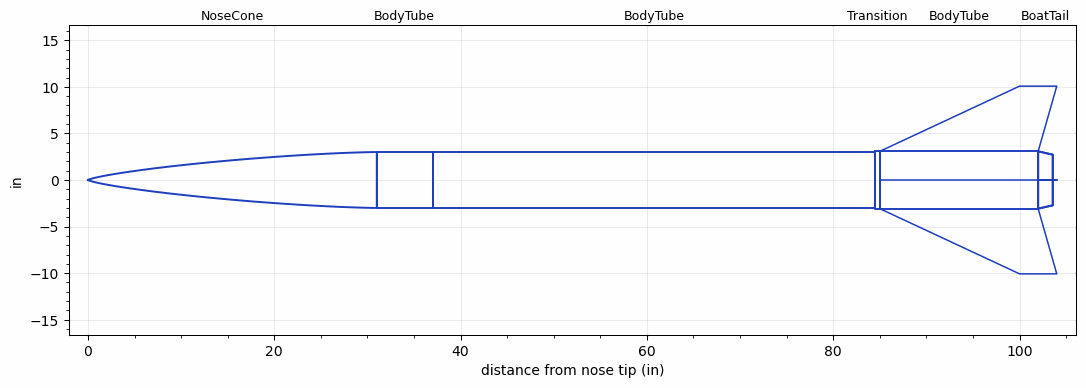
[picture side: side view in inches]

<RASAeroDocument>
 <FileVersion>2</FileVersion>
 <RocketDesign>
  <NoseCone>
   <Length>30.9999</Length>
   <Diameter>6</Diameter>
   <Shape>Von Karman Ogive</Shape>
   <BluntRadius>0.08</BluntRadius>
   <Location>0</Location>
  </NoseCone>
  <BodyTube>
   <Length>6</Length>
   <Diameter>6</Diameter>
   <Location>30.9999</Location>
  </BodyTube>
  <BodyTube>
   <Length>47.5</Length>
   <Diameter>6</Diameter>
   <RailGuideDiameter>0.63</RailGuideDiameter>
   <RailGuideHeight>0.44</RailGuideHeight>
   <Location>36.9999</Location>
  </BodyTube>
  <Transition>
   <Length>0.5</Length>
   <Diameter>6.15</Diameter>
   <Location>84.4999</Location>
   <RearDiameter>6.15</RearDiameter>
  </Transition>
  <BodyTube>
   <Length>17</Length>
   <Diameter>6.15</Diameter>
   <Location>84.9999</Location>
   <BoattailLength>1.57</BoattailLength>
   <BoattailRearDiameter>5.44</BoattailRearDiameter>
   <Fin>
    <Count>4</Count>
    <Chord>17</Chord>
    <Span>7</Span>
    <SweepDistance>15</SweepDistance>
    <TipChord>4</TipChord>
    <Thickness>0.3125</Thickness>
    <LERadius>0.08</LERadius>
    <Location>17</Location>
    <AirfoilSection>Hexagonal</AirfoilSection>
    <FX1>0.75</FX1>
    <FX3>0.75</FX3>
   </Fin>
  </BodyTube>
  <BoatTail>
   <Length>1.57</Length>
   <Diameter>6.15</Diameter>
   <RearDiameter>5.44</RearDiameter>
   <Location>101.9999</Location>
  </BoatTail>
  <Surface>Rough Camouflage Paint</Surface>
  <ModifiedBarrowman>True</ModifiedBarrowman>
  <Turbulence>True</Turbulence>
  <UseBooster1>False</UseBooster1>
  <UseBooster2>False</UseBooster2>
 </RocketDesign>
 <LaunchSite>
  <Altitude>2000</Altitude>
  <Pressure>29.92</Pressure>
  <RodAngle>2</RodAngle>
  <RodLength>240</RodLength>
  <Temperature>85</Temperature>
  <WindSpeed>5</WindSpeed>
 </LaunchSite>
 <Recovery>
  <Altitude1>0</Altitude1>
  <Altitude2>0</Altitude2>
  <DeviceType1>None</DeviceType1>
  <DeviceType2>None</DeviceType2>
  <Event1>False</Event1>
  <Event2>False</Event2>
  <Size1>0</Size1>
  <Size2>0</Size2>
  <EventType1>None</EventType1>
  <EventType2>None</EventType2>
  <CD1>0</CD1>
  <CD2>0</CD2>
 </Recovery>
 <SimulationList>
  <Simulation>
   <SustainerEngine>P6750  (TRT)</SustainerEngine>
   <SustainerLaunchWt>116</SustainerLaunchWt>
   <SustainerNozzleDiameter>4</SustainerNozzleDiameter>
   <SustainerCG>67.5</SustainerCG>
   <SustainerIgnitionDelay>0</SustainerIgnitionDelay>
   <Booster1SeparationDelay>0</Booster1SeparationDelay>
   <Booster1IgnitionDelay>0</Booster1IgnitionDelay>
   <IncludeBooster1>False</IncludeBooster1>
   <Booster2Delay>0</Booster2Delay>
   <IncludeBooster2>False</IncludeBooster2>
   <TimetoApogee>66.0657</TimetoApogee>
   <MaxAltitude>80890.1</MaxAltitude>
   <MaxVelocity>3694.235</MaxVelocity>
   <OptimumWt>87.72498</OptimumWt>
   <OptimumMaxAlt>87.72498</OptimumMaxAlt>
  </Simulation>
  <Simulation>
   <SustainerLaunchWt>110.4978</SustainerLaunchWt>
   <SustainerCG>67.6143</SustainerCG>
   <SustainerIgnitionDelay>0</SustainerIgnitionDelay>
   <Booster1SeparationDelay>0</Booster1SeparationDelay>
   <Booster1IgnitionDelay>0</Booster1IgnitionDelay>
   <IncludeBooster1>False</IncludeBooster1>
   <Booster2Delay>0</Booster2Delay>
   <IncludeBooster2>False</IncludeBooster2>
  </Simulation>
 </SimulationList>
</RASAeroDocument>
